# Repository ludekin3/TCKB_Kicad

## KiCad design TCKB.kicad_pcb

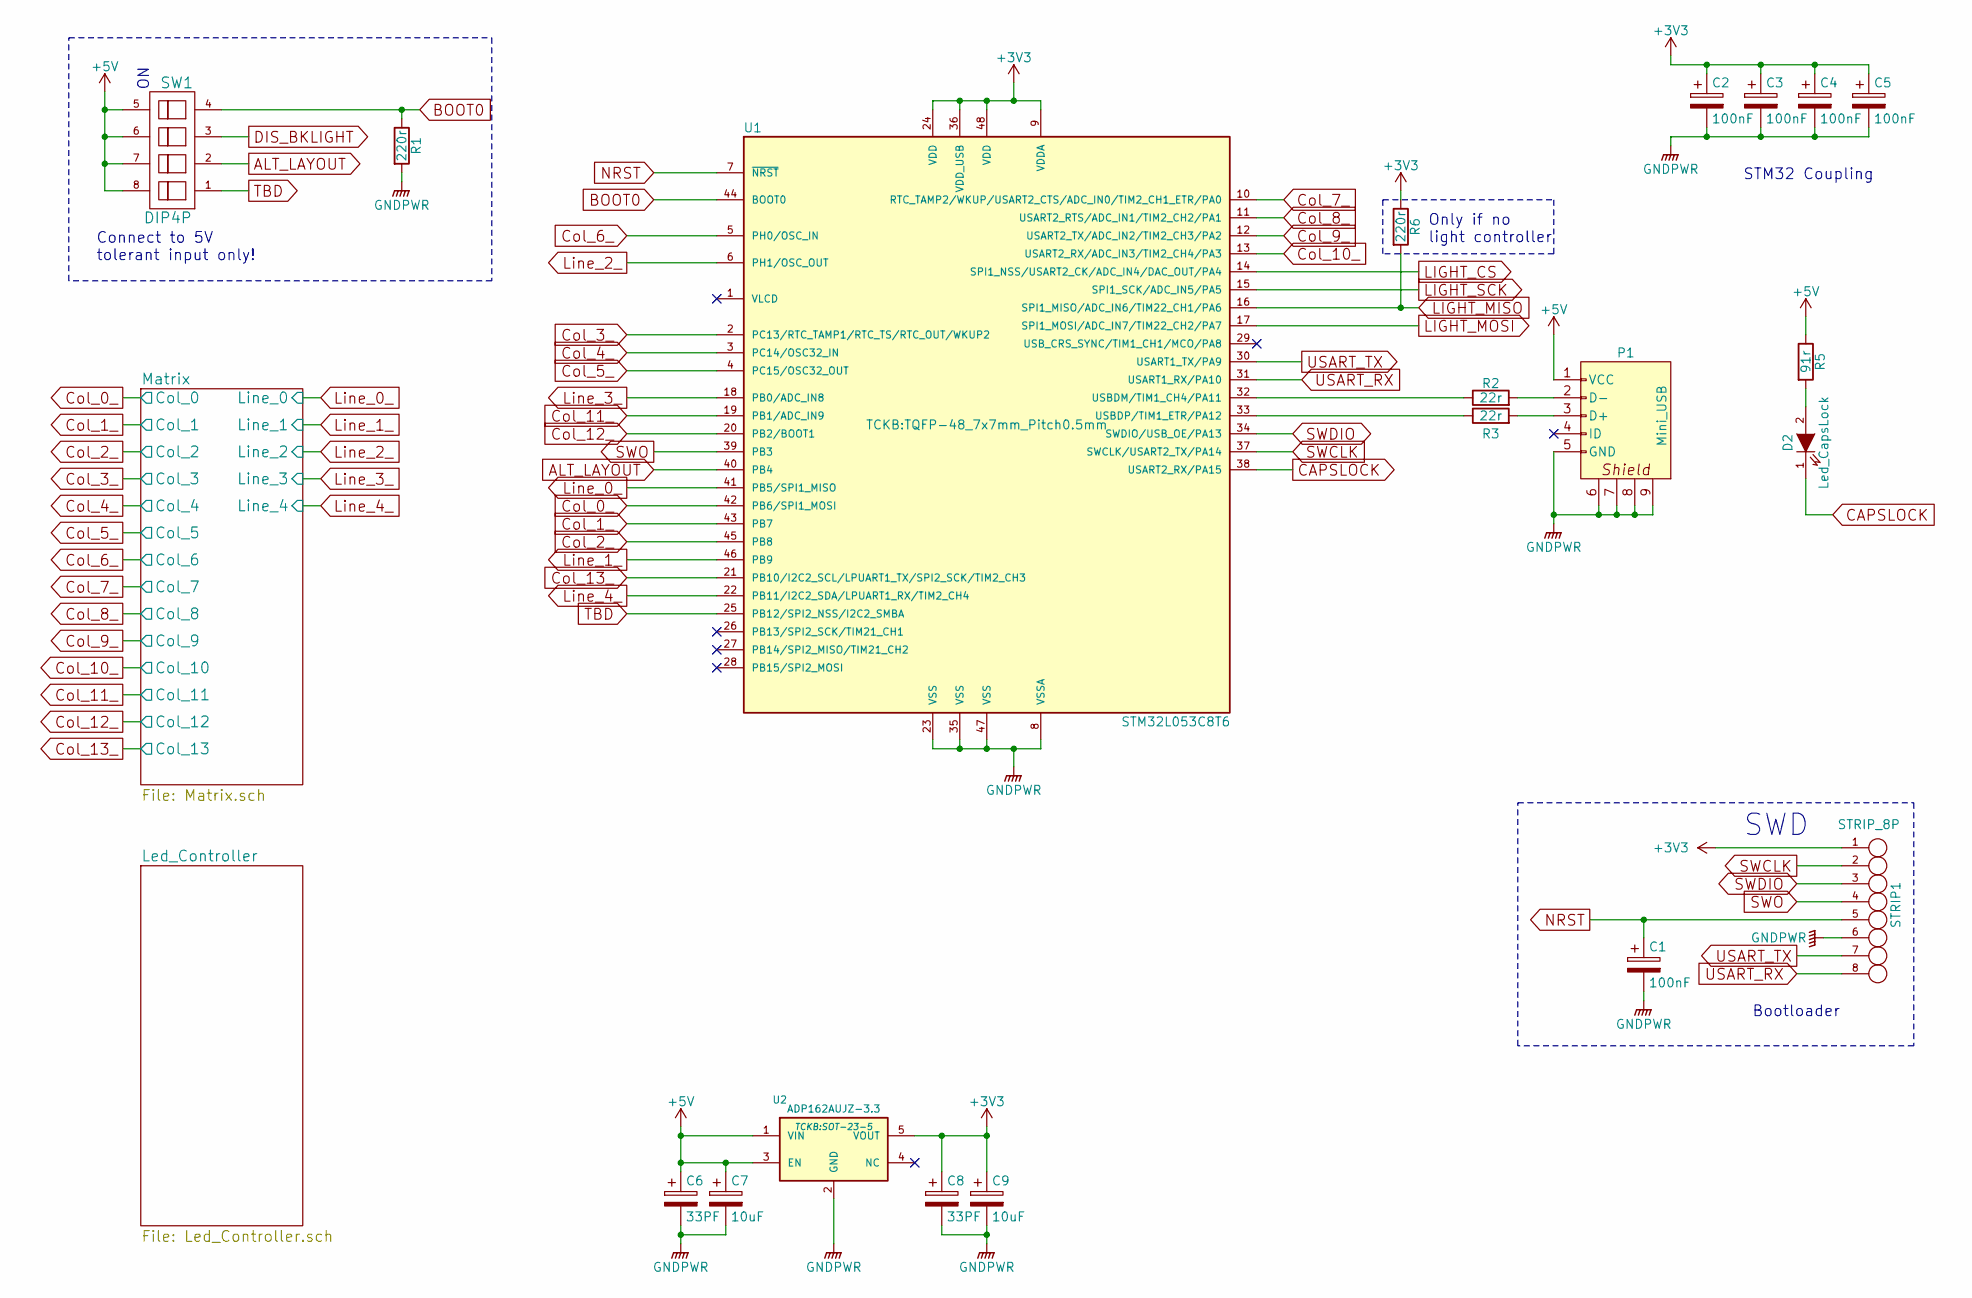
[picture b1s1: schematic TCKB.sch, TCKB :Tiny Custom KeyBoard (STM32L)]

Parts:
C1, C2, C3, C4, C5: 100nF; C_0805
C6, C8: 33PF; C_0805
C7, C9: 10uF; C_0805
D2: Led_CapsLock; CHERRY_MX_LED
P1: Mini_USB; USB_Mini-B
R1, R6: 220r; R_0805
R2, R3: 22r; R_0805
R5: 91r; R_0805
STRIP1: STRIP_8P; SlantedStrip8p
SW1: DIP4P; DIPSWITCH-8_SMD
U1: STM32L053C8T6; TQFP-48_7x7mm_Pitch0.5mm
U2: ADP162AUJZ-3.3; SOT-23-5

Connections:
+3V3: C2.1, C3.1, C4.1, C5.1, C8.1, C9.1, R6.1, STRIP1.1, U1.9 (VDDA), U1.24 (VDD), U1.36 (VDD_USB), U1.48 (VDD), U2.5 (VOUT)
+5V: C6.1, C7.1, P1.1 (VCC), R5.1, SW1.5, SW1.6, SW1.7, SW1.8, U2.1 (VIN), U2.3 (EN); also elsewhere on the board
ALT_LAYOUT: SW1.2, U1.40 (PB4)
BOOT0: R1.1, SW1.4, U1.44 (BOOT0); also elsewhere on the board
CAPSLOCK: D2.1 (K), U1.38 (USART2_RX/PA15)
Col_0_: U1.42 (PB6/SPI1_MOSI); also elsewhere on the board
Col_1_: U1.43 (PB7); also elsewhere on the board
Col_2_: U1.45 (PB8); also elsewhere on the board
Col_3_: U1.2 (PC13/RTC_TAMP1/RTC_TS/RTC_OUT/WKUP2); also elsewhere on the board
Col_4_: U1.3 (PC14/OSC32_IN); also elsewhere on the board
Col_5_: U1.4 (PC15/OSC32_OUT); also elsewhere on the board
Col_6_: U1.5 (PH0/OSC_IN); also elsewhere on the board
Col_7_: U1.10 (RTC_TAMP2/WKUP/USART2_CTS/ADC_IN0/TIM2_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); also elsewhere on the board
Col_8_: U1.11 (USART2_RTS/ADC_IN1/TIM2_CH2/PA1); also elsewhere on the board
Col_9_: U1.12 (USART2_TX/ADC_IN2/TIM2_CH3/PA2); also elsewhere on the board
Col_10_: U1.13 (USART2_RX/ADC_IN3/TIM2_CH4/PA3); also elsewhere on the board
Col_11_: U1.19 (PB1/ADC_IN9); also elsewhere on the board
Col_12_: U1.20 (PB2/BOOT1); also elsewhere on the board
Col_13_: U1.21 (PB10/I2C2_SCL/LPUART1_TX/SPI2_SCK/TIM2_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); also elsewhere on the board
DIS_BKLIGHT: SW1.3; also elsewhere on the board
GNDPWR: C1.2, C2.2, C3.2, C4.2, C5.2, C6.2, C7.2, C8.2, C9.2, P1.5 (GND), P1.6, P1.7, P1.8, P1.9, R1.2, STRIP1.6, U1.8 (VSSA), U1.23 (VSS), U1.35 (VSS), U1.47 (VSS), U2.2 (GND); also elsewhere on the board
LIGHT_CS: U1.14 (SPI1_NSS/USART2_CK/ADC_IN4/DAC_OUT/PA4); also elsewhere on the board
LIGHT_MISO: R6.2, U1.16 (SPI1_MISO/ADC_IN6/TIM22_CH1/PA6); also elsewhere on the board
LIGHT_MOSI: U1.17 (SPI1_MOSI/ADC_IN7/TIM22_CH2/PA7); also elsewhere on the board
LIGHT_SCK: U1.15 (SPI1_SCK/ADC_IN5/PA5); also elsewhere on the board
Line_0_: U1.41 (PB5/SPI1_MISO); also elsewhere on the board
Line_1_: U1.46 (PB9); also elsewhere on the board
Line_2_: U1.6 (PH1/OSC_OUT); also elsewhere on the board
Line_3_: U1.18 (PB0/ADC_IN8); also elsewhere on the board
Line_4_: U1.22 (PB11/I2C2_SDA/LPUART1_RX/TIM2_CH4); also elsewhere on the board
NRST: C1.1, STRIP1.5, U1.7 (~NRST)
unnamed: D2.2 (A), R5.2
unnamed: P1.2 (D-), R2.2
unnamed: P1.3 (D+), R3.2
unnamed: R2.1, U1.32 (USBDM/TIM1_CH4/PA11)
unnamed: R3.1, U1.33 (USBDP/TIM1_ETR/PA12)
SWCLK: STRIP1.2, U1.37 (SWCLK/USART2_TX/PA14)
SWDIO: STRIP1.3, U1.34 (SWDIO/USB_OE/PA13)
SWO: STRIP1.4, U1.39 (PB3)
TBD: SW1.1, U1.25 (PB12/SPI2_NSS/I2C2_SMBA); also elsewhere on the board
USART_RX: STRIP1.8, U1.31 (USART1_RX/PA10)
USART_TX: STRIP1.7, U1.30 (USART1_TX/PA9)

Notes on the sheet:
SWD
STM32 Coupling
Bootloader
Only if no light controller
Connect to 5V tolerant input only!

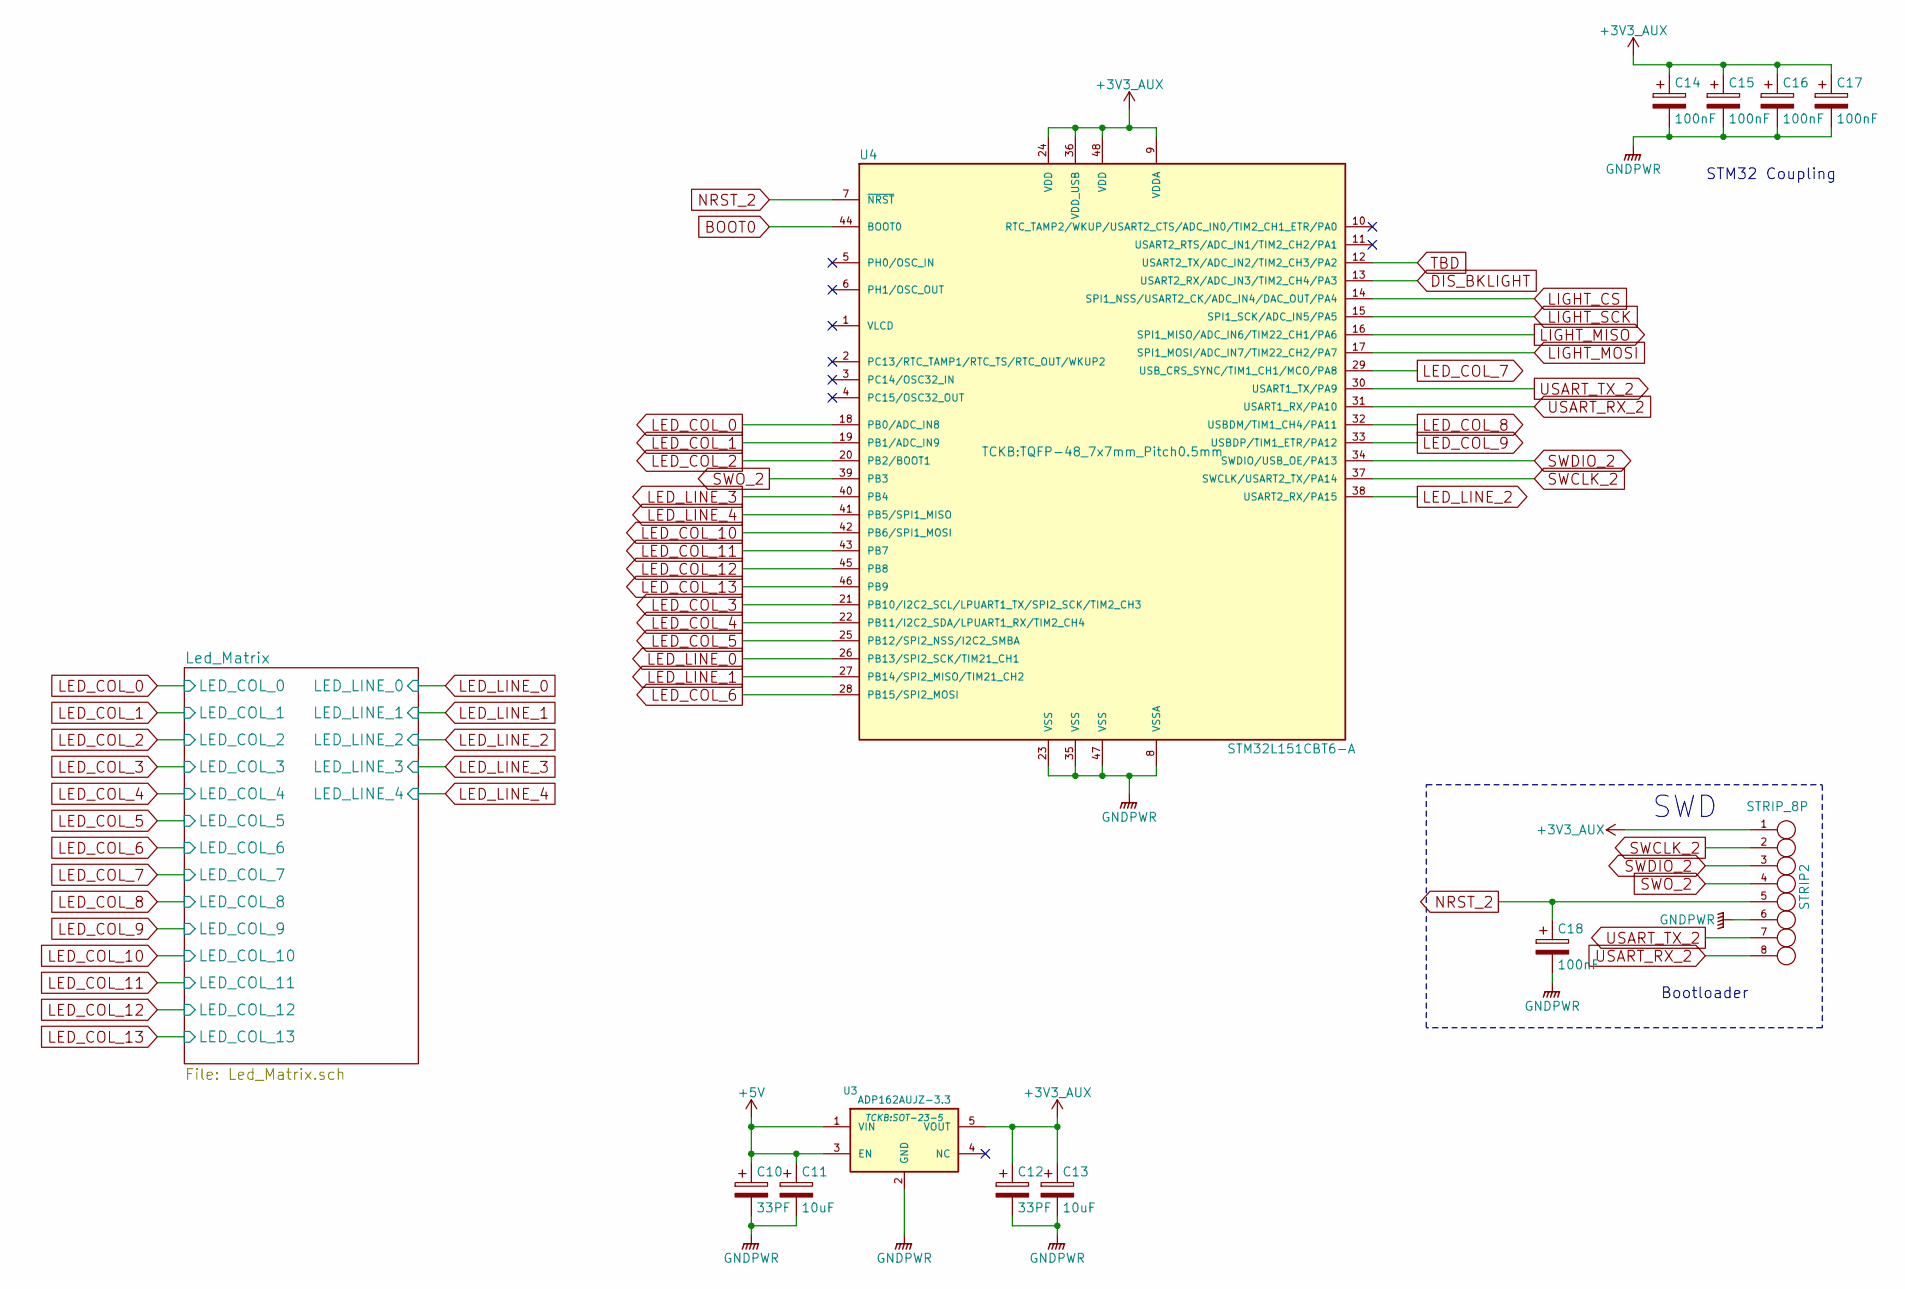
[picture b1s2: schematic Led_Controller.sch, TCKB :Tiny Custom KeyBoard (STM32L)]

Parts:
C10, C12: 33PF; C_0805
C11, C13: 10uF; C_0805
C14, C15, C16, C17, C18: 100nF; C_0805
STRIP2: STRIP_8P; SlantedStrip8p
U3: ADP162AUJZ-3.3; SOT-23-5
U4: STM32L151CBT6-A; TQFP-48_7x7mm_Pitch0.5mm

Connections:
+3V3_AUX: C12.1, C13.1, C14.1, C15.1, C16.1, C17.1, STRIP2.1, U3.5 (VOUT), U4.9 (VDDA), U4.24 (VDD), U4.36 (VDD_USB), U4.48 (VDD)
+5V: C10.1, C11.1, U3.1 (VIN), U3.3 (EN); also elsewhere on the board
BOOT0: U4.44 (BOOT0); also elsewhere on the board
DIS_BKLIGHT: U4.13 (USART2_RX/ADC_IN3/TIM2_CH4/PA3); also elsewhere on the board
GNDPWR: C10.2, C11.2, C12.2, C13.2, C14.2, C15.2, C16.2, C17.2, C18.2, STRIP2.6, U3.2 (GND), U4.8 (VSSA), U4.23 (VSS), U4.35 (VSS), U4.47 (VSS); also elsewhere on the board
LED_COL_0: U4.18 (PB0/ADC_IN8); also elsewhere on the board
LED_COL_1: U4.19 (PB1/ADC_IN9); also elsewhere on the board
LED_COL_2: U4.20 (PB2/BOOT1); also elsewhere on the board
LED_COL_3: U4.21 (PB10/I2C2_SCL/LPUART1_TX/SPI2_SCK/TIM2_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); also elsewhere on the board
LED_COL_4: U4.22 (PB11/I2C2_SDA/LPUART1_RX/TIM2_CH4); also elsewhere on the board
LED_COL_5: U4.25 (PB12/SPI2_NSS/I2C2_SMBA); also elsewhere on the board
LED_COL_6: U4.28 (PB15/SPI2_MOSI); also elsewhere on the board
LED_COL_7: U4.29 (USB_CRS_SYNC/TIM1_CH1/MCO/PA8); also elsewhere on the board
LED_COL_8: U4.32 (USBDM/TIM1_CH4/PA11); also elsewhere on the board
LED_COL_9: U4.33 (USBDP/TIM1_ETR/PA12); also elsewhere on the board
LED_COL_10: U4.42 (PB6/SPI1_MOSI); also elsewhere on the board
LED_COL_11: U4.43 (PB7); also elsewhere on the board
LED_COL_12: U4.45 (PB8); also elsewhere on the board
LED_COL_13: U4.46 (PB9); also elsewhere on the board
LED_LINE_0: U4.26 (PB13/SPI2_SCK/TIM21_CH1); also elsewhere on the board
LED_LINE_1: U4.27 (PB14/SPI2_MISO/TIM21_CH2); also elsewhere on the board
LED_LINE_2: U4.38 (USART2_RX/PA15); also elsewhere on the board
LED_LINE_3: U4.40 (PB4); also elsewhere on the board
LED_LINE_4: U4.41 (PB5/SPI1_MISO); also elsewhere on the board
LIGHT_CS: U4.14 (SPI1_NSS/USART2_CK/ADC_IN4/DAC_OUT/PA4); also elsewhere on the board
LIGHT_MISO: U4.16 (SPI1_MISO/ADC_IN6/TIM22_CH1/PA6); also elsewhere on the board
LIGHT_MOSI: U4.17 (SPI1_MOSI/ADC_IN7/TIM22_CH2/PA7); also elsewhere on the board
LIGHT_SCK: U4.15 (SPI1_SCK/ADC_IN5/PA5); also elsewhere on the board
NRST_2: C18.1, STRIP2.5, U4.7 (~NRST)
SWCLK_2: STRIP2.2, U4.37 (SWCLK/USART2_TX/PA14)
SWDIO_2: STRIP2.3, U4.34 (SWDIO/USB_OE/PA13)
SWO_2: STRIP2.4, U4.39 (PB3)
TBD: U4.12 (USART2_TX/ADC_IN2/TIM2_CH3/PA2); also elsewhere on the board
USART_RX_2: STRIP2.8, U4.31 (USART1_RX/PA10)
USART_TX_2: STRIP2.7, U4.30 (USART1_TX/PA9)

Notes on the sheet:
STM32 Coupling
SWD
Bootloader

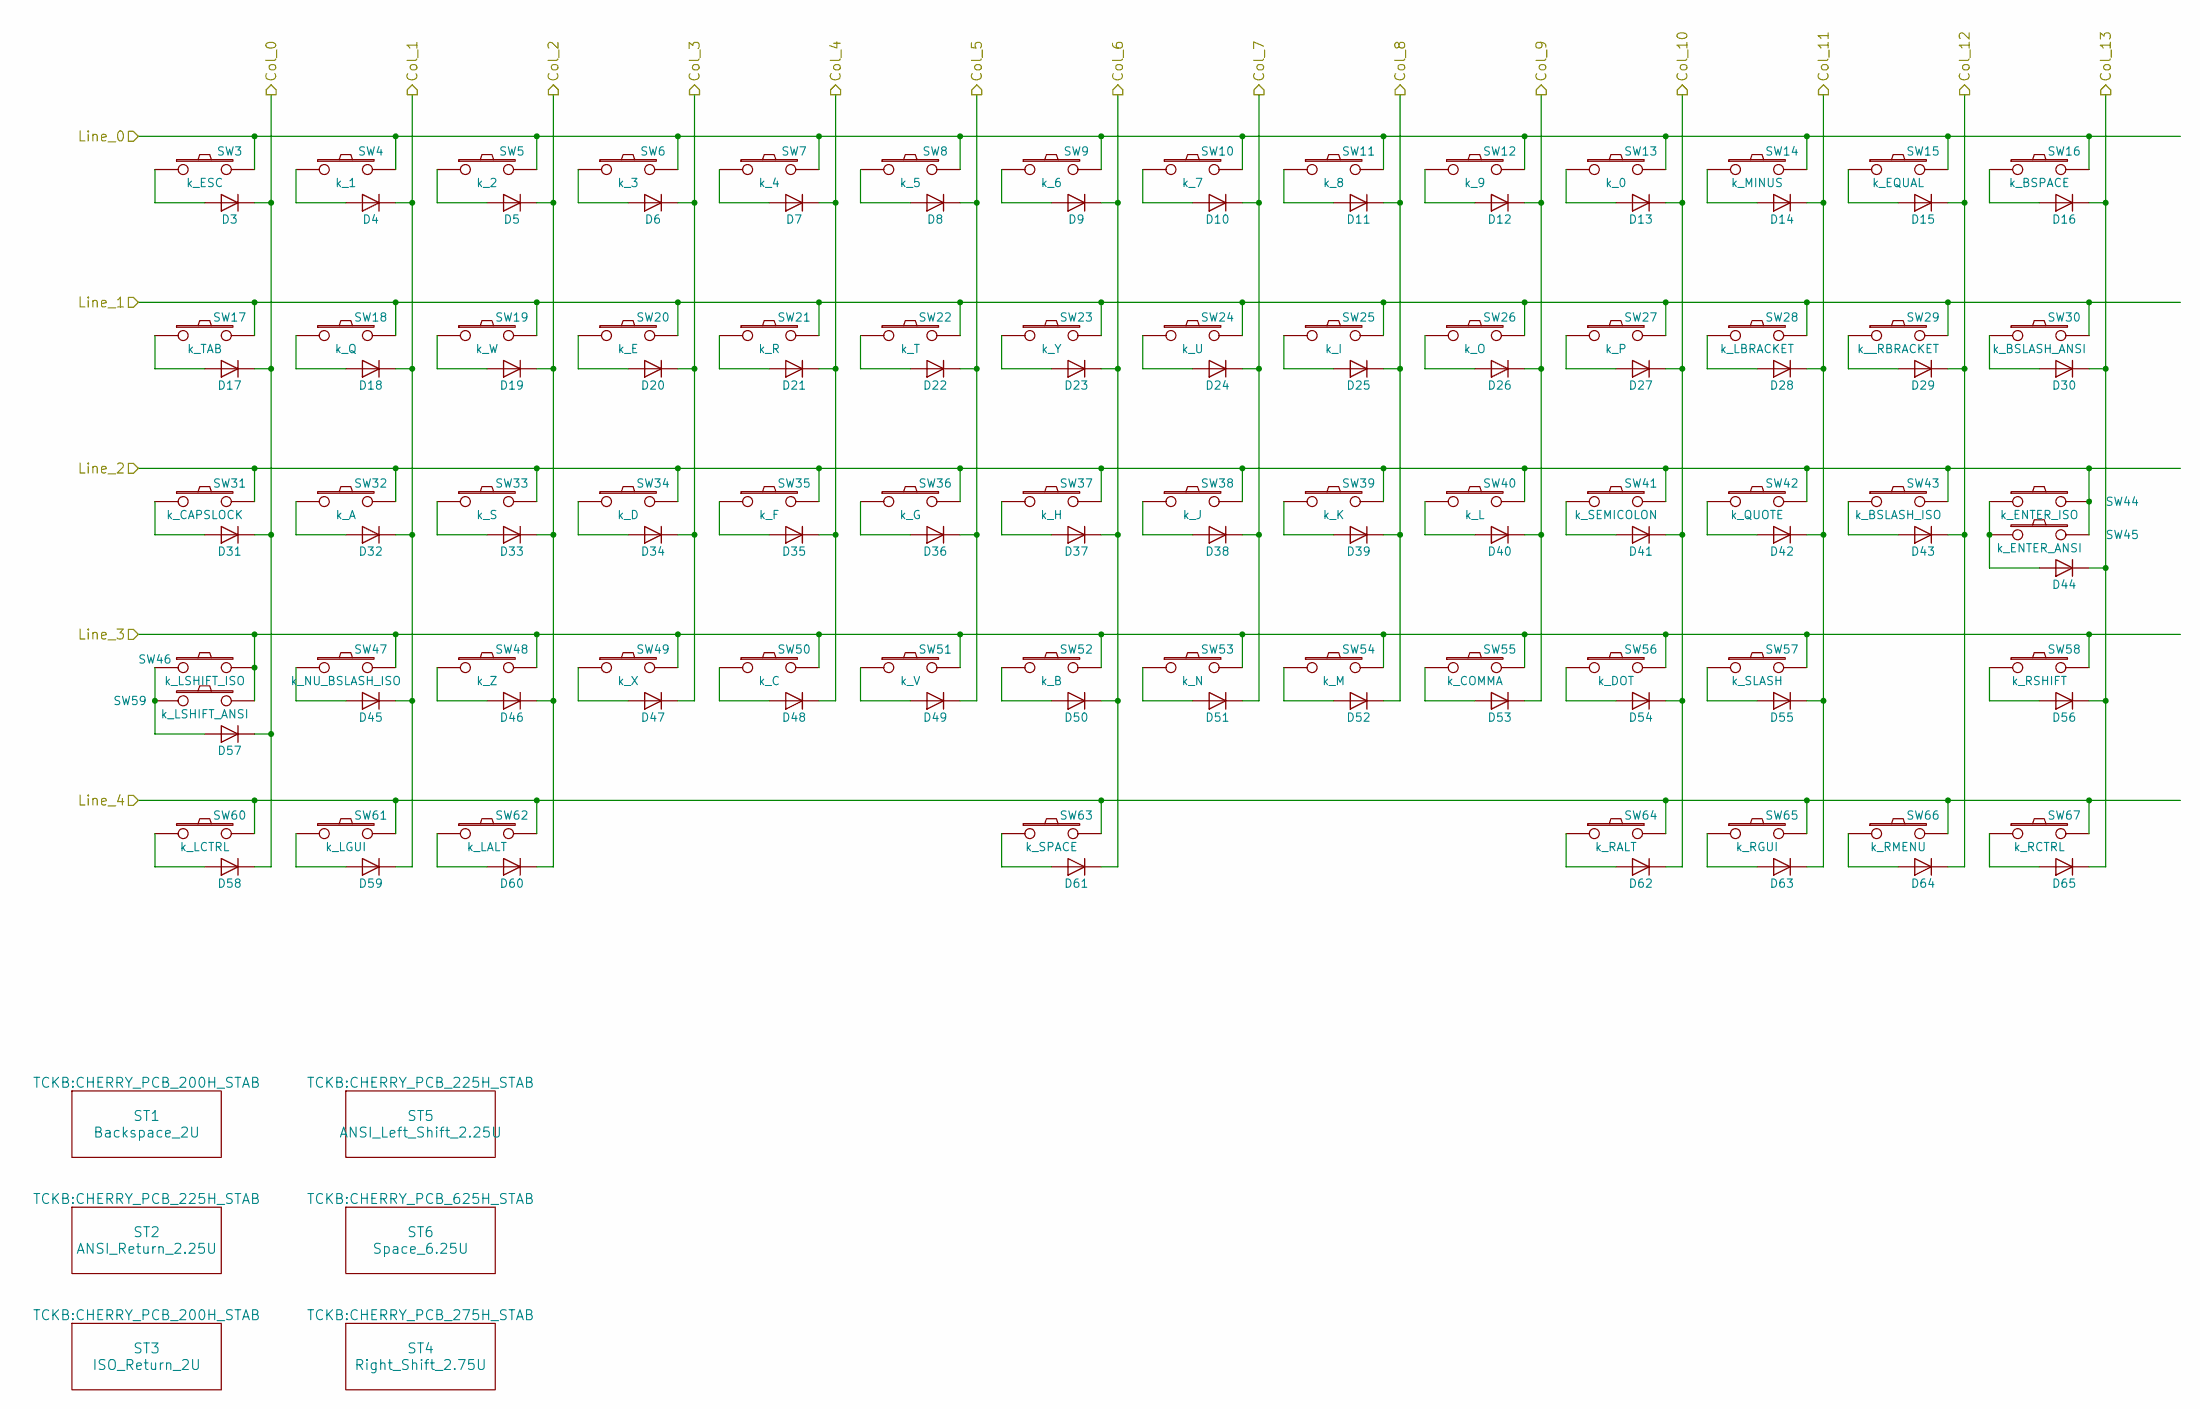
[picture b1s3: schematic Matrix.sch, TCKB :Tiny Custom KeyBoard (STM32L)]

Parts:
D3, D4, D5, D6, D7, D8, D9, D10, D11, D12, D13, D14, D15, D16, D17, D18, D19, D20, D21, D22, D23, D24, D25, D26, D27, D28, D29, D30, D31, D32, D33, D34, D35, D36, D37, D38, D39, D40, D41, D42, D43, D44, D45, D46, D47, D48, D49, D50, D51, D52, D53, D54, D55, D56, D57, D58, D59, D60, D61, D62, D63, D64, D65: 1N4148; MiniMELF_2mm
ST1: Backspace_2U; CHERRY_PCB_200H_STAB
ST2: ANSI_Return_2.25U; CHERRY_PCB_225H_STAB
ST3: ISO_Return_2U; CHERRY_PCB_200H_STAB
ST4: Right_Shift_2.75U; CHERRY_PCB_275H_STAB
ST5: ANSI_Left_Shift_2.25U; CHERRY_PCB_225H_STAB
ST6: Space_6.25U; CHERRY_PCB_625H_STAB
SW3: k_ESC; CHERRY_PCB_100H
SW4: k_1; CHERRY_PCB_100H
SW5: k_2; CHERRY_PCB_100H
SW6: k_3; CHERRY_PCB_100H
SW7: k_4; CHERRY_PCB_100H
SW8: k_5; CHERRY_PCB_100H
SW9: k_6; CHERRY_PCB_100H
SW10: k_7; CHERRY_PCB_100H
SW11: k_8; CHERRY_PCB_100H
SW12: k_9; CHERRY_PCB_100H
SW13: k_0; CHERRY_PCB_100H
SW14: k_MINUS; CHERRY_PCB_100H
SW15: k_EQUAL; CHERRY_PCB_100H
SW16: k_BSPACE; CHERRY_PCB_200H_SW
SW17: k_TAB; CHERRY_PCB_150H
SW18: k_Q; CHERRY_PCB_100H
SW19: k_W; CHERRY_PCB_100H
SW20: k_E; CHERRY_PCB_100H
SW21: k_R; CHERRY_PCB_100H
SW22: k_T; CHERRY_PCB_100H
SW23: k_Y; CHERRY_PCB_100H
SW24: k_U; CHERRY_PCB_100H
SW25: k_I; CHERRY_PCB_100H
SW26: k_O; CHERRY_PCB_100H
SW27: k_P; CHERRY_PCB_100H
SW28: k_LBRACKET; CHERRY_PCB_100H
SW29: k__RBRACKET; CHERRY_PCB_100H
SW30: k_BSLASH_ANSI; CHERRY_PCB_150H
SW31: k_CAPSLOCK; CHERRY_PCB_175H
SW32: k_A; CHERRY_PCB_100H
SW33: k_S; CHERRY_PCB_100H
SW34: k_D; CHERRY_PCB_100H
SW35: k_F; CHERRY_PCB_100H
SW36: k_G; CHERRY_PCB_100H
SW37: k_H; CHERRY_PCB_100H
SW38: k_J; CHERRY_PCB_100H
SW39: k_K; CHERRY_PCB_100H
SW40: k_L; CHERRY_PCB_100H
SW41: k_SEMICOLON; CHERRY_PCB_100H
SW42: k_QUOTE; CHERRY_PCB_100H
SW43: k_BSLASH_ISO; CHERRY_PCB_100H
SW44: k_ENTER_ISO; CHERRY_PCB_200H_SW
SW45: k_ENTER_ANSI; CHERRY_PCB_225H_SW
SW46: k_LSHIFT_ISO; CHERRY_PCB_125H
SW47: k_NU_BSLASH_ISO; CHERRY_PCB_100H
SW48: k_Z; CHERRY_PCB_100H
SW49: k_X; CHERRY_PCB_100H
SW50: k_C; CHERRY_PCB_100H
SW51: k_V; CHERRY_PCB_100H
SW52: k_B; CHERRY_PCB_100H
SW53: k_N; CHERRY_PCB_100H
SW54: k_M; CHERRY_PCB_100H
SW55: k_COMMA; CHERRY_PCB_100H
SW56: k_DOT; CHERRY_PCB_100H
SW57: k_SLASH; CHERRY_PCB_100H
SW58: k_RSHIFT; CHERRY_PCB_275H_SW
SW59: k_LSHIFT_ANSI; CHERRY_PCB_225H_SW
SW60: k_LCTRL; CHERRY_PCB_125H
SW61: k_LGUI; CHERRY_PCB_125H
SW62: k_LALT; CHERRY_PCB_125H
SW63: k_SPACE; CHERRY_PCB_625H_SW
SW64: k_RALT; CHERRY_PCB_125H
SW65: k_RGUI; CHERRY_PCB_125H
SW66: k_RMENU; CHERRY_PCB_125H
SW67: k_RCTRL; CHERRY_PCB_125H

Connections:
Col_0_: D3.1 (K), D17.1 (K), D31.1 (K), D57.1 (K), D58.1 (K); also elsewhere on the board
Col_1_: D4.1 (K), D18.1 (K), D32.1 (K), D45.1 (K), D59.1 (K); also elsewhere on the board
Col_2_: D5.1 (K), D19.1 (K), D33.1 (K), D46.1 (K), D60.1 (K); also elsewhere on the board
Col_3_: D6.1 (K), D20.1 (K), D34.1 (K), D47.1 (K); also elsewhere on the board
Col_4_: D7.1 (K), D21.1 (K), D35.1 (K), D48.1 (K); also elsewhere on the board
Col_5_: D8.1 (K), D22.1 (K), D36.1 (K), D49.1 (K); also elsewhere on the board
Col_6_: D9.1 (K), D23.1 (K), D37.1 (K), D50.1 (K), D61.1 (K); also elsewhere on the board
Col_7_: D10.1 (K), D24.1 (K), D38.1 (K), D51.1 (K); also elsewhere on the board
Col_8_: D11.1 (K), D25.1 (K), D39.1 (K), D52.1 (K); also elsewhere on the board
Col_9_: D12.1 (K), D26.1 (K), D40.1 (K), D53.1 (K); also elsewhere on the board
Col_10_: D13.1 (K), D27.1 (K), D41.1 (K), D54.1 (K), D62.1 (K); also elsewhere on the board
Col_11_: D14.1 (K), D28.1 (K), D42.1 (K), D55.1 (K), D63.1 (K); also elsewhere on the board
Col_12_: D15.1 (K), D29.1 (K), D43.1 (K), D64.1 (K); also elsewhere on the board
Col_13_: D16.1 (K), D30.1 (K), D44.1 (K), D56.1 (K), D65.1 (K); also elsewhere on the board
Line_0_: SW3.2, SW4.2, SW5.2, SW6.2, SW7.2, SW8.2, SW9.2, SW10.2, SW11.2, SW12.2, SW13.2, SW14.2, SW15.2, SW16.2; also elsewhere on the board
Line_1_: SW17.2, SW18.2, SW19.2, SW20.2, SW21.2, SW22.2, SW23.2, SW24.2, SW25.2, SW26.2, SW27.2, SW28.2, SW29.2, SW30.2; also elsewhere on the board
Line_2_: SW31.2, SW32.2, SW33.2, SW34.2, SW35.2, SW36.2, SW37.2, SW38.2, SW39.2, SW40.2, SW41.2, SW42.2, SW43.2, SW44.2, SW45.2; also elsewhere on the board
Line_3_: SW46.2, SW47.2, SW48.2, SW49.2, SW50.2, SW51.2, SW52.2, SW53.2, SW54.2, SW55.2, SW56.2, SW57.2, SW58.2, SW59.2; also elsewhere on the board
Line_4_: SW60.2, SW61.2, SW62.2, SW63.2, SW64.2, SW65.2, SW66.2, SW67.2; also elsewhere on the board
unnamed: D3.2 (A), SW3.1
unnamed: D4.2 (A), SW4.1
unnamed: D5.2 (A), SW5.1
unnamed: D6.2 (A), SW6.1
unnamed: D7.2 (A), SW7.1
unnamed: D8.2 (A), SW8.1
unnamed: D9.2 (A), SW9.1
unnamed: D10.2 (A), SW10.1
unnamed: D11.2 (A), SW11.1
unnamed: D12.2 (A), SW12.1
unnamed: D13.2 (A), SW13.1
unnamed: D14.2 (A), SW14.1
unnamed: D15.2 (A), SW15.1
unnamed: D16.2 (A), SW16.1
unnamed: D17.2 (A), SW17.1
unnamed: D18.2 (A), SW18.1
unnamed: D19.2 (A), SW19.1
unnamed: D20.2 (A), SW20.1
unnamed: D21.2 (A), SW21.1
unnamed: D22.2 (A), SW22.1
unnamed: D23.2 (A), SW23.1
unnamed: D24.2 (A), SW24.1
unnamed: D25.2 (A), SW25.1
unnamed: D26.2 (A), SW26.1
unnamed: D27.2 (A), SW27.1
unnamed: D28.2 (A), SW28.1
unnamed: D29.2 (A), SW29.1
unnamed: D30.2 (A), SW30.1
unnamed: D31.2 (A), SW31.1
unnamed: D32.2 (A), SW32.1
unnamed: D33.2 (A), SW33.1
unnamed: D34.2 (A), SW34.1
unnamed: D35.2 (A), SW35.1
unnamed: D36.2 (A), SW36.1
unnamed: D37.2 (A), SW37.1
unnamed: D38.2 (A), SW38.1
unnamed: D39.2 (A), SW39.1
unnamed: D40.2 (A), SW40.1
unnamed: D41.2 (A), SW41.1
unnamed: D42.2 (A), SW42.1
unnamed: D43.2 (A), SW43.1
unnamed: D44.2 (A), SW44.1, SW45.1
unnamed: D45.2 (A), SW47.1
unnamed: D46.2 (A), SW48.1
unnamed: D47.2 (A), SW49.1
unnamed: D48.2 (A), SW50.1
unnamed: D49.2 (A), SW51.1
unnamed: D50.2 (A), SW52.1
unnamed: D51.2 (A), SW53.1
unnamed: D52.2 (A), SW54.1
unnamed: D53.2 (A), SW55.1
unnamed: D54.2 (A), SW56.1
unnamed: D55.2 (A), SW57.1
unnamed: D56.2 (A), SW58.1
unnamed: D57.2 (A), SW46.1, SW59.1
unnamed: D58.2 (A), SW60.1
unnamed: D59.2 (A), SW61.1
unnamed: D60.2 (A), SW62.1
unnamed: D61.2 (A), SW63.1
unnamed: D62.2 (A), SW64.1
unnamed: D63.2 (A), SW65.1
unnamed: D64.2 (A), SW66.1
unnamed: D65.2 (A), SW67.1

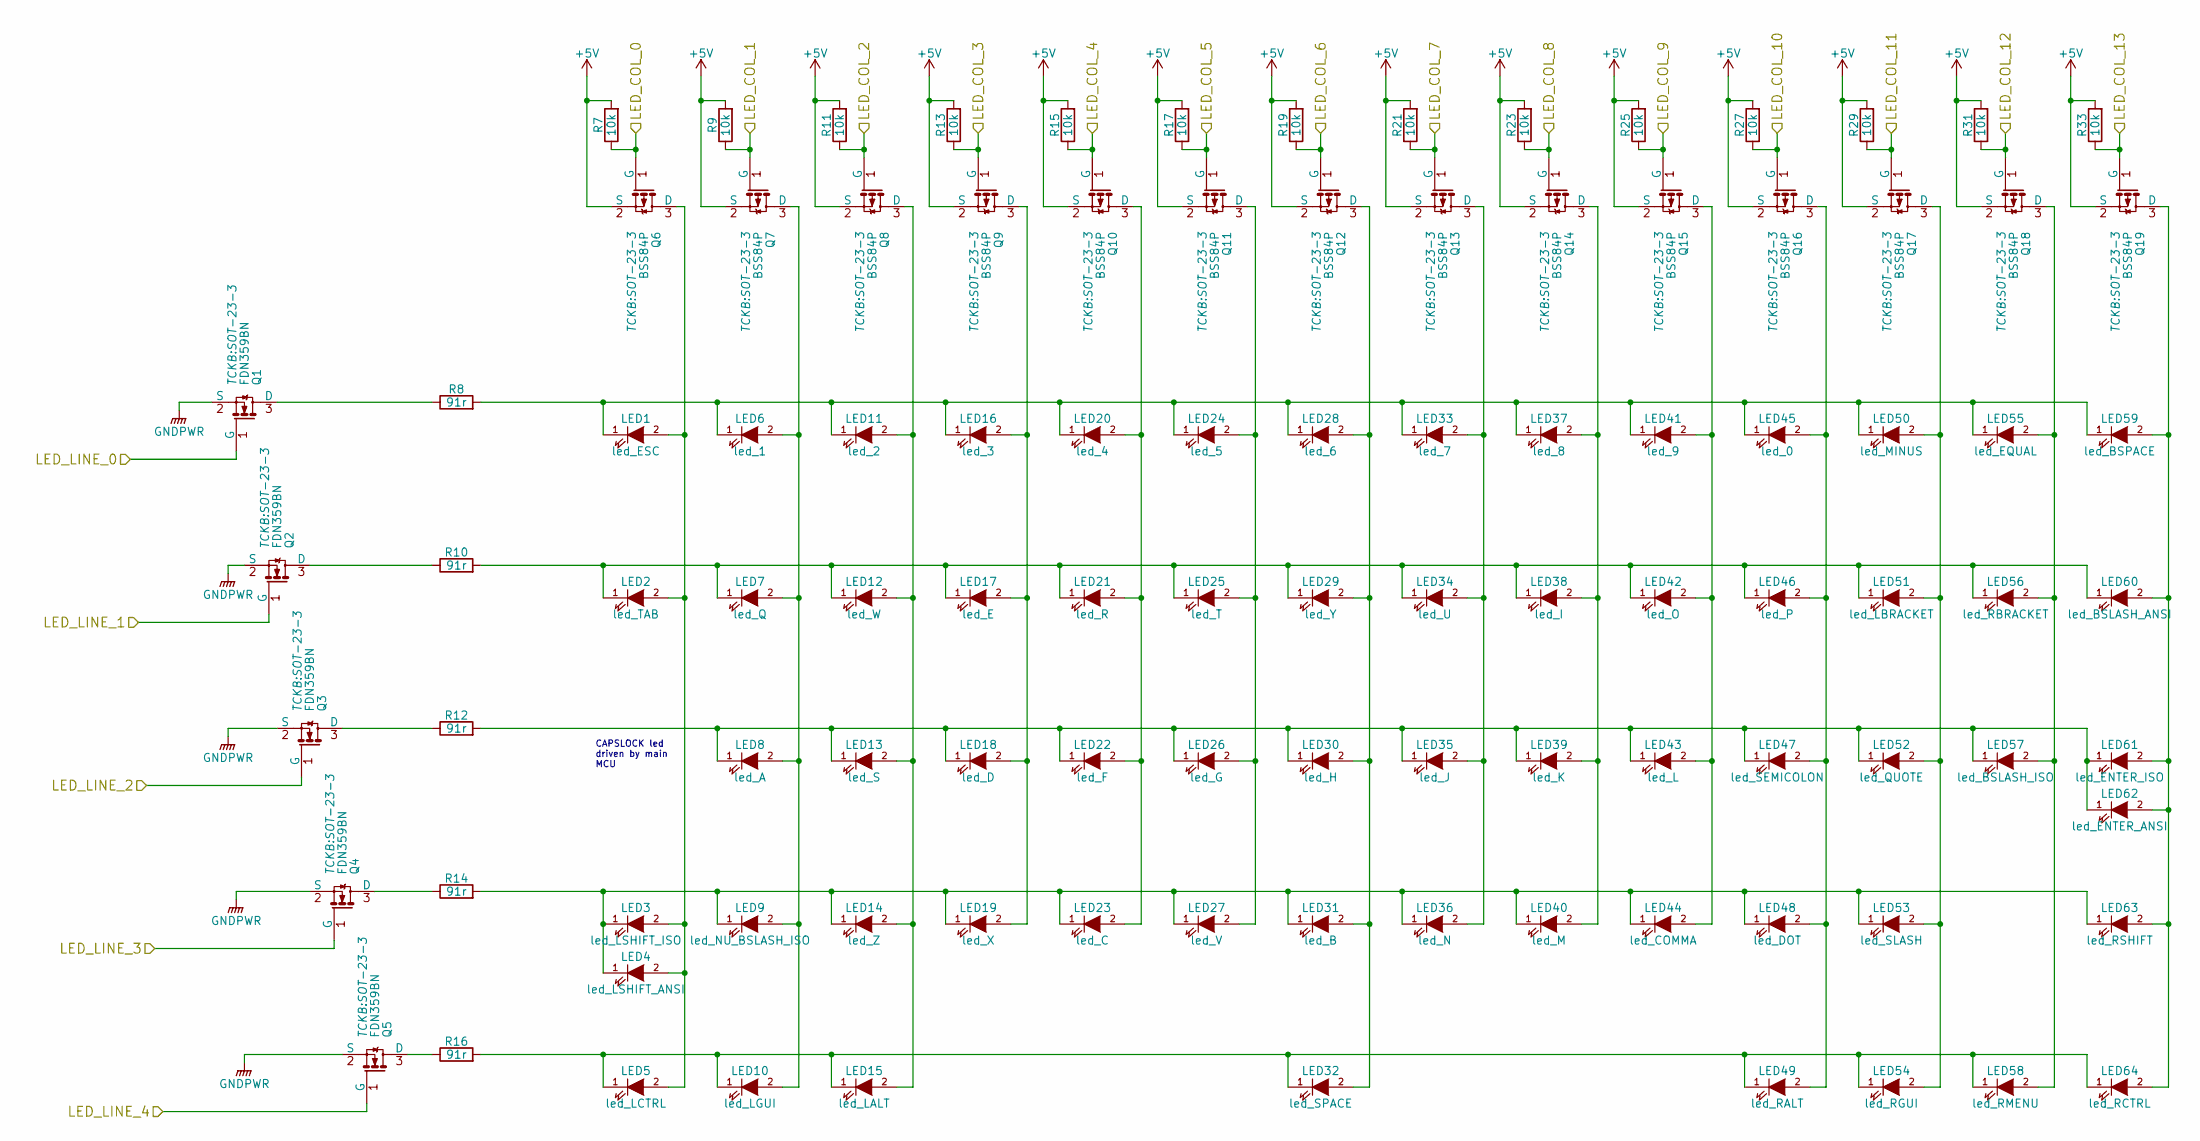
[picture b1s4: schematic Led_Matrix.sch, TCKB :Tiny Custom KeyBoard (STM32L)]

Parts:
LED1: led_ESC; CHERRY_MX_LED
LED2: led_TAB; CHERRY_MX_LED
LED3: led_LSHIFT_ISO; CHERRY_MX_LED
LED4: led_LSHIFT_ANSI; CHERRY_MX_LED
LED5: led_LCTRL; CHERRY_MX_LED
LED6: led_1; CHERRY_MX_LED
LED7: led_Q; CHERRY_MX_LED
LED8: led_A; CHERRY_MX_LED
LED9: led_NU_BSLASH_ISO; CHERRY_MX_LED
LED10: led_LGUI; CHERRY_MX_LED
LED11: led_2; CHERRY_MX_LED
LED12: led_W; CHERRY_MX_LED
LED13: led_S; CHERRY_MX_LED
LED14: led_Z; CHERRY_MX_LED
LED15: led_LALT; CHERRY_MX_LED
LED16: led_3; CHERRY_MX_LED
LED17: led_E; CHERRY_MX_LED
LED18: led_D; CHERRY_MX_LED
LED19: led_X; CHERRY_MX_LED
LED20: led_4; CHERRY_MX_LED
LED21: led_R; CHERRY_MX_LED
LED22: led_F; CHERRY_MX_LED
LED23: led_C; CHERRY_MX_LED
LED24: led_5; CHERRY_MX_LED
LED25: led_T; CHERRY_MX_LED
LED26: led_G; CHERRY_MX_LED
LED27: led_V; CHERRY_MX_LED
LED28: led_6; CHERRY_MX_LED
LED29: led_Y; CHERRY_MX_LED
LED30: led_H; CHERRY_MX_LED
LED31: led_B; CHERRY_MX_LED
LED32: led_SPACE; CHERRY_MX_LED
LED33: led_7; CHERRY_MX_LED
LED34: led_U; CHERRY_MX_LED
LED35: led_J; CHERRY_MX_LED
LED36: led_N; CHERRY_MX_LED
LED37: led_8; CHERRY_MX_LED
LED38: led_I; CHERRY_MX_LED
LED39: led_K; CHERRY_MX_LED
LED40: led_M; CHERRY_MX_LED
LED41: led_9; CHERRY_MX_LED
LED42: led_O; CHERRY_MX_LED
LED43: led_L; CHERRY_MX_LED
LED44: led_COMMA; CHERRY_MX_LED
LED45: led_0; CHERRY_MX_LED
LED46: led_P; CHERRY_MX_LED
LED47: led_SEMICOLON; CHERRY_MX_LED
LED48: led_DOT; CHERRY_MX_LED
LED49: led_RALT; CHERRY_MX_LED
LED50: led_MINUS; CHERRY_MX_LED
LED51: led_LBRACKET; CHERRY_MX_LED
LED52: led_QUOTE; CHERRY_MX_LED
LED53: led_SLASH; CHERRY_MX_LED
LED54: led_RGUI; CHERRY_MX_LED
LED55: led_EQUAL; CHERRY_MX_LED
LED56: led_RBRACKET; CHERRY_MX_LED
LED57: led_BSLASH_ISO; CHERRY_MX_LED
LED58: led_RMENU; CHERRY_MX_LED
LED59: led_BSPACE; CHERRY_MX_LED
LED60: led_BSLASH_ANSI; CHERRY_MX_LED
LED61: led_ENTER_ISO; CHERRY_MX_LED
LED62: led_ENTER_ANSI; CHERRY_MX_LED
LED63: led_RSHIFT; CHERRY_MX_LED
LED64: led_RCTRL; CHERRY_MX_LED
Q1, Q2, Q3, Q4, Q5: FDN359BN; SOT-23-3
Q6, Q7, Q8, Q9, Q10, Q11, Q12, Q13, Q14, Q15, Q16, Q17, Q18, Q19: BSS84P; SOT-23-3
R7, R9, R11, R13, R15, R17, R19, R21, R23, R25, R27, R29, R31, R33: 10k; R_0805
R8, R10, R12, R14, R16: 91r; R_0805

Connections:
+5V: Q6.2 (S), Q7.2 (S), Q8.2 (S), Q9.2 (S), Q10.2 (S), Q11.2 (S), Q12.2 (S), Q13.2 (S), Q14.2 (S), Q15.2 (S), Q16.2 (S), Q17.2 (S), Q18.2 (S), Q19.2 (S), R7.2, R9.2, R11.2, R13.2, R15.2, R17.2, R19.2, R21.2, R23.2, R25.2, R27.2, R29.2, R31.2, R33.2; also elsewhere on the board
GNDPWR: Q1.2 (S), Q2.2 (S), Q3.2 (S), Q4.2 (S), Q5.2 (S); also elsewhere on the board
LED_COL_0: Q6.1 (G), R7.1; also elsewhere on the board
LED_COL_1: Q7.1 (G), R9.1; also elsewhere on the board
LED_COL_2: Q8.1 (G), R11.1; also elsewhere on the board
LED_COL_3: Q9.1 (G), R13.1; also elsewhere on the board
LED_COL_4: Q10.1 (G), R15.1; also elsewhere on the board
LED_COL_5: Q11.1 (G), R17.1; also elsewhere on the board
LED_COL_6: Q12.1 (G), R19.1; also elsewhere on the board
LED_COL_7: Q13.1 (G), R21.1; also elsewhere on the board
LED_COL_8: Q14.1 (G), R23.1; also elsewhere on the board
LED_COL_9: Q15.1 (G), R25.1; also elsewhere on the board
LED_COL_10: Q16.1 (G), R27.1; also elsewhere on the board
LED_COL_11: Q17.1 (G), R29.1; also elsewhere on the board
LED_COL_12: Q18.1 (G), R31.1; also elsewhere on the board
LED_COL_13: Q19.1 (G), R33.1; also elsewhere on the board
LED_LINE_0: Q1.1 (G); also elsewhere on the board
LED_LINE_1: Q2.1 (G); also elsewhere on the board
LED_LINE_2: Q3.1 (G); also elsewhere on the board
LED_LINE_3: Q4.1 (G); also elsewhere on the board
LED_LINE_4: Q5.1 (G); also elsewhere on the board
unnamed: LED1.1 (K), LED6.1 (K), LED11.1 (K), LED16.1 (K), LED20.1 (K), LED24.1 (K), LED28.1 (K), LED33.1 (K), LED37.1 (K), LED41.1 (K), LED45.1 (K), LED50.1 (K), LED55.1 (K), LED59.1 (K), R8.2
unnamed: LED1.2 (A), LED2.2 (A), LED3.2 (A), LED4.2 (A), LED5.2 (A), Q6.3 (D)
unnamed: LED5.1 (K), LED10.1 (K), LED15.1 (K), LED32.1 (K), LED49.1 (K), LED54.1 (K), LED58.1 (K), LED64.1 (K), R16.2
unnamed: LED6.2 (A), LED7.2 (A), LED8.2 (A), LED9.2 (A), LED10.2 (A), Q7.3 (D)
unnamed: LED11.2 (A), LED12.2 (A), LED13.2 (A), LED14.2 (A), LED15.2 (A), Q8.3 (D)
unnamed: LED2.1 (K), LED7.1 (K), LED12.1 (K), LED17.1 (K), LED21.1 (K), LED25.1 (K), LED29.1 (K), LED34.1 (K), LED38.1 (K), LED42.1 (K), LED46.1 (K), LED51.1 (K), LED56.1 (K), LED60.1 (K), R10.2
unnamed: LED8.1 (K), LED13.1 (K), LED18.1 (K), LED22.1 (K), LED26.1 (K), LED30.1 (K), LED35.1 (K), LED39.1 (K), LED43.1 (K), LED47.1 (K), LED52.1 (K), LED57.1 (K), LED61.1 (K), LED62.1 (K), R12.2
unnamed: LED3.1 (K), LED4.1 (K), LED9.1 (K), LED14.1 (K), LED19.1 (K), LED23.1 (K), LED27.1 (K), LED31.1 (K), LED36.1 (K), LED40.1 (K), LED44.1 (K), LED48.1 (K), LED53.1 (K), LED63.1 (K), R14.2
unnamed: LED16.2 (A), LED17.2 (A), LED18.2 (A), LED19.2 (A), Q9.3 (D)
unnamed: LED20.2 (A), LED21.2 (A), LED22.2 (A), LED23.2 (A), Q10.3 (D)
unnamed: LED24.2 (A), LED25.2 (A), LED26.2 (A), LED27.2 (A), Q11.3 (D)
unnamed: LED28.2 (A), LED29.2 (A), LED30.2 (A), LED31.2 (A), LED32.2 (A), Q12.3 (D)
unnamed: LED33.2 (A), LED34.2 (A), LED35.2 (A), LED36.2 (A), Q13.3 (D)
unnamed: LED37.2 (A), LED38.2 (A), LED39.2 (A), LED40.2 (A), Q14.3 (D)
unnamed: LED41.2 (A), LED42.2 (A), LED43.2 (A), LED44.2 (A), Q15.3 (D)
unnamed: LED45.2 (A), LED46.2 (A), LED47.2 (A), LED48.2 (A), LED49.2 (A), Q16.3 (D)
unnamed: LED50.2 (A), LED51.2 (A), LED52.2 (A), LED53.2 (A), LED54.2 (A), Q17.3 (D)
unnamed: LED55.2 (A), LED56.2 (A), LED57.2 (A), LED58.2 (A), Q18.3 (D)
unnamed: LED59.2 (A), LED60.2 (A), LED61.2 (A), LED62.2 (A), LED63.2 (A), LED64.2 (A), Q19.3 (D)
unnamed: Q1.3 (D), R8.1
unnamed: Q2.3 (D), R10.1
unnamed: Q3.3 (D), R12.1
unnamed: Q4.3 (D), R14.1
unnamed: Q5.3 (D), R16.1

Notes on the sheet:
CAPSLOCK led driven by main MCU

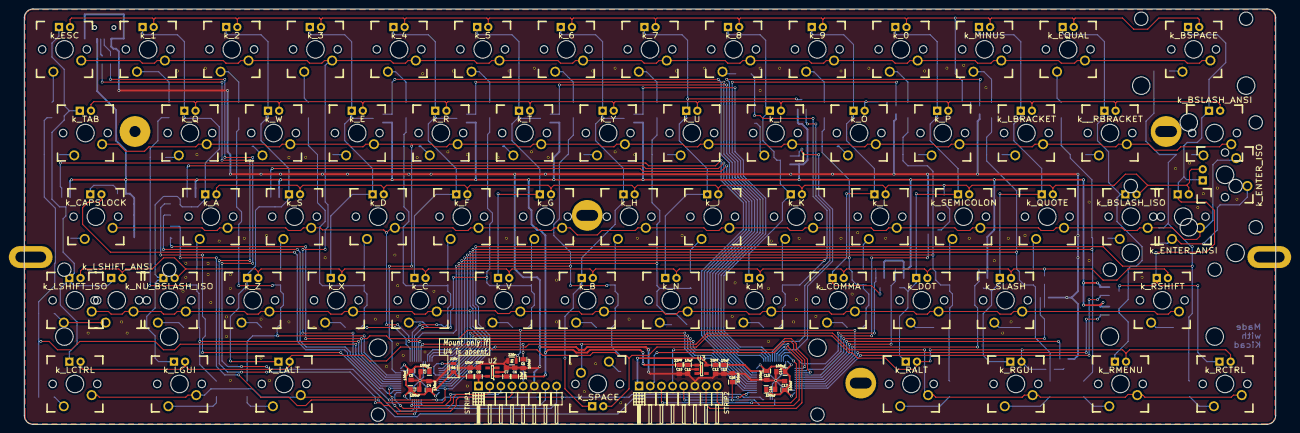
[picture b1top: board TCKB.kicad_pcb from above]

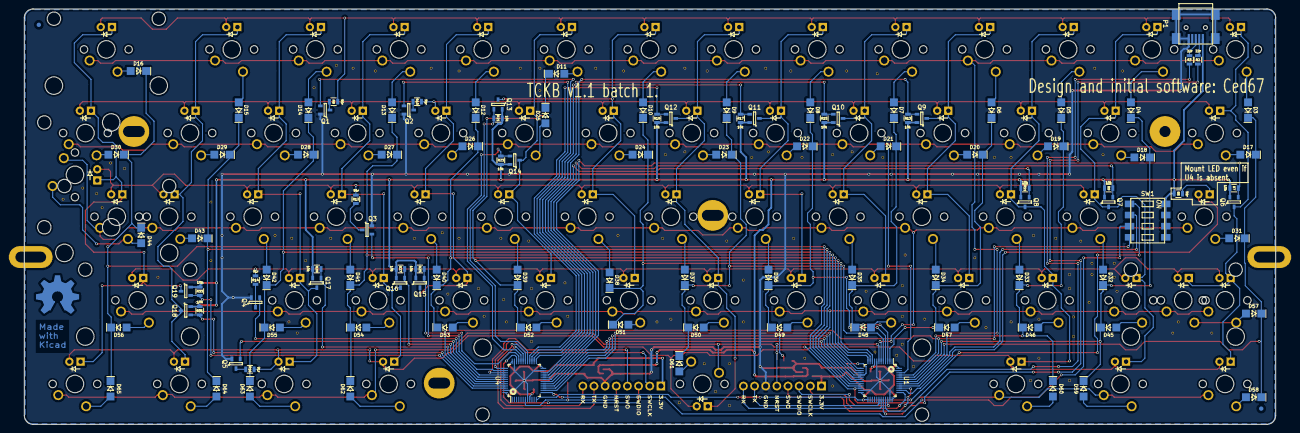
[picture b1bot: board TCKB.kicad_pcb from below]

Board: 2 copper layers, 285.0 x 94.6 mm, 277 parts (112 on the bottom side), 155 nets.

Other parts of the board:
FID: FIDUCIAL
FID#2: FIDUCIAL
HOLE: VAL**; PKRHSL
HOLE#2: VAL**; PKRHSL
HOLE#3, HOLE#4, HOLE#5: VAL**; PKRH
HOLE#6: VAL**; PKRHC
OSHW_COPPER_10MM: VAL**; OSHW_COPPER_10MM

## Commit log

2020-03-14 Symbol Rescue
